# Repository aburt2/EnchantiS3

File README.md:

# EnchantiS3
 Repository for hardware and firmware for the EnchantiS3 board. The EnchantiS3 is a board based on the ESP32-S3 WROOM 2 module from Espressif. It includes a fuel gauge and inertial measurement unit (IMU). The board can be powered from both the USB-C port or a 3.7V lithium ion battery.

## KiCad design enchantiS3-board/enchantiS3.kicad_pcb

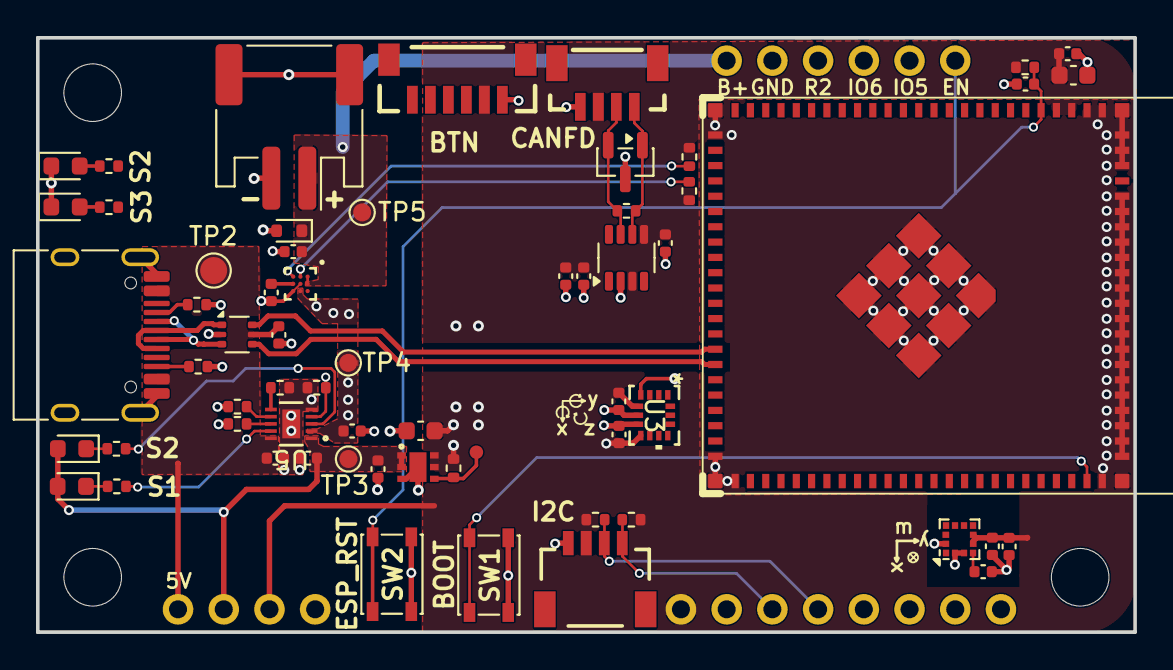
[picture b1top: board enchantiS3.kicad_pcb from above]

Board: 4 copper layers, 61.0 x 33.0 mm, 66 parts (0 on the bottom side), 33 nets.

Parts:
BAT1: JST_SMD_2.0; Battery_JST_2pin
BOARDLAYOUT1: LAYOUT; enchantis31-layout
C1, C5, C6, C9, C11, C16: 1uF; C_0402_1005Metric
C2, C7, C8, C12, C14, C15, C19, C20: 0.1uF; C_0402_1005Metric
C3: 2.2uF; C_0402_1005Metric
C4: 10uF; C_0402_1005Metric
C10, C13: 10uF; C_0603_1608Metric
C17: 0.47uF; C_0402_1005Metric
D1: DZ2S051X0L; D_SOD-523
D2: NUP2105L; SOT-23
H1, H2, H3: MountingHole; MountingHole_3.2mm_M3_DIN965
J1: USB_C_Receptacle_USB2.0; USB_C_Receptacle_HRO_TYPE-C-31-M-12
J2: Conn_01x06; JST_1x06_P1.0mm_Vertical_SMD
J3: Qwiic_Connector; JST_1x04_P1.0mm_Horizontal_SMD
LED1: Orange; LED_0603_1608Metric
LED2: Blue; LED_0603_1608Metric
LED3: Yellow; LED_0603_1608Metric
LED4: Red; LED_0603_1608Metric
R3, R4: 2k; R_0402_1005Metric
R5, R6, R15, R19: 10k; R_0402_1005Metric
R7, R9, R17, R18: 2k2; R_0402_1005Metric
R8, R10: 1k; R_0402_1005Metric
R11, R13: 5K1; R_0402_1005Metric
R12: 13k; R_0402_1005Metric
R14: 0.43k; R_0402_1005Metric
R16: 120; R_0402_1005Metric
SW1: BOOT; SW_SPST_PTS810
SW2: ESP_RST; SW_SPST_PTS810
TOUCH2: JST-SH-1x04 1.0mm; JST_SMD_1.0mm-4_Vertical
TP1: 0.75mm; TestPoint-0.75mm
TP2: TestPoint; TestPoint_Pad_D1.5mm
TP3, TP4, TP5: TestPoint; TestPoint_Pad_D1.0mm
U1: USBLC6-2P6; SOT-666
U2: NCP187; NCV8187_ONS
U3: ICM-42670-P; LGA14_2P5X3X0P91_TDK
U4: ESP32-S31-WROOM-3
U5: BQ25185DLHR; WSON10_DLH_TEX
U6: MAX17262REWL+T; MAX17262
U7: TCAN3413DDFR; TSOT-23-8_DDF_TEX
U8: LIS3MDL; LGA-12_2x2mm_P0.5mm

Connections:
+3V3: BOARDLAYOUT1.2.1 (3v3), BOARDLAYOUT1.3.3 (VDD), C2.1, C3.1, C6.1, C7.1, C8.1, C10.1, C13.1, C14.1, C16.1, C19.1, J2.2, J3.2 (3v3), R5.2, R6.2, R7.2, R9.2, R17.1, R18.1, TOUCH2.2 (3v3), U2.5 (SNS), U2.6 (OUT), U3.5 (VDDIO), U3.8 (VDD), U4.3 (3V3), U4.4 (3V3), U7.3 (VCC), U7.5 (VIO), U8.5 (Vdd), U8.6 (Vdd_IO)
+BATT: BAT1.1 (+), BOARDLAYOUT1.1.1 (VBAT), C15.1, D1.1 (K), TP5.1 (1_1), U6.A1 (TH), U6.A2 (BATT)
/MCU/BOOT: SW1.1, U4.71 (GPIO61)
/MCU/EN: BOARDLAYOUT1.1.6 (EN), C9.1, R5.1, SW2.1, U4.5 (EN)
/MCU/USBD+: U1.6 (I/O1), U4.40 (USB_DP)
/MCU/USBD-: U1.4 (I/O2), U4.41 (USB_DM)
/Motion Sensing/C1: C20.1, U8.4 (C1)
/Peripherals/CAN_H: D2.2 (K), R16.2, TOUCH2.3 (SDA), U7.7 (CANH)
/Peripherals/CAN_L: D2.1 (K), R16.1, TOUCH2.4 (SCL), U7.6 (CANL)
/Peripherals/SCL2: BOARDLAYOUT1.2.3 (SCL), J3.4 (SCL), R7.1
/Peripherals/SDA2: BOARDLAYOUT1.2.4 (SDA), J3.3 (SDA), R9.1
/Power System/FG_SCL: R18.2, U6.B1 (SCL)
/Power System/FG_SDA: R17.2, U6.C1 (SDA)
/Power System/ISET: R14.1, U5.8 (ISET)
/Power System/LED0: LED4.1 (K), R4.1
/Power System/LED1: LED3.1 (K), R3.1
/Power System/PG: R6.1, TP1.1 (1_1), U2.4 (PG)
/Power System/REG: C17.1, U6.C2 (REG)
/Power System/STAT1: R3.2, U5.9 (STAT1)
/Power System/STAT2: R4.2, U5.3 (STAT2)
/Power System/TS: R15.2, U5.6 (TS/MR)
/Power System/VSET: R12.1, U5.7 (ILIM/VSET)
/Power System/~CE: R19.2, U5.4 (~CE)
/USB/CC1: J1.A5 (CC1), R11.1
/USB/CC2: J1.B5 (CC2), R13.1
/USB/D+: J1.A6 (D+), J1.B6 (D+), U1.1 (I/O1)
/USB/D-: J1.A7 (D-), J1.B7 (D-), U1.3 (I/O2)
CHRG+: C5.1, TP4.1 (1_1), U5.2 (BAT), U6.B3 (SYS)
GND: BAT1.2 (-), BAT1.MP (mp), BOARDLAYOUT1.1.2 (GND), BOARDLAYOUT1.2.2 (GND), BOARDLAYOUT1.2.8 (GND), BOARDLAYOUT1.3.4 (GND), C1.2, C2.2, C3.2, C4.2, C5.2, C6.2, C7.2, C8.2, C9.2, C10.2, C11.2, C12.2, C13.2, C14.2, C15.2, C16.2, C17.2, C19.2, C20.2, D1.2 (A), D2.3 (A), J1.A1 (GND), J1.A12 (GND), J1.B1 (GND), J1.B12 (GND), J1.SH (SHIELD), J2.1, J3.1 (GND), LED1.1 (K), LED2.1 (K), R11.2, R12.2, R13.2, R14.2, R15.1, R19.1, SW1.2, SW2.2, TOUCH2.1 (GND), U1.2 (GND), U2.3 (GND), U2.7 (GND), U3.6 (GND), U3.7 (FSYNC), U4.1 (GND), U4.2 (GND), U4.26 (GND), U4.47 (GND), U4.48 (GND), U4.72 (GND), U4.73 (GND), U4.74 (GND), U4.75 (GND), U4.76 (GND), U4.77 (GND), U4.78 (GND), U4.79 (GND), U4.80 (GND), U4.81 (GND), U4.82 (GND), U4.83 (GND), U4.84 (GND), U4.85 (GND), U4.86 (GND), U4.87 (GND), U4.88 (GND), U4.89 (GND), U4.90 (GND), U4.92 (GND), U4.93 (GND), U4.94 (GND), U4.95 (GND), U4.96 (GND), U4.97 (GND), U4.98 (GND), U4.99 (GND), U5.5 (GND), U5.11 (EPAD), U6.B2 (ALRT), U6.C3 (GND), U7.2 (GND), U8.2 (GND), U8.3 (GND), U8.12 (GND)
unnamed: LED1.2 (A), R10.2
unnamed: LED2.2 (A), R8.2
SYS: BOARDLAYOUT1.3.2 (SYS), C4.1, C11.1, LED3.2 (A), LED4.2 (A), TP3.1 (1_1), U2.1 (IN), U2.2 (EN), U5.1 (SYS)
VUSB: BOARDLAYOUT1.3.1 (5v), C1.1, C12.1, J1.A4 (VBUS), J1.A9 (VBUS), J1.B4 (VBUS), J1.B9 (VBUS), TP2.1 (1_1), U1.5 (VBUS), U5.10 (IN)

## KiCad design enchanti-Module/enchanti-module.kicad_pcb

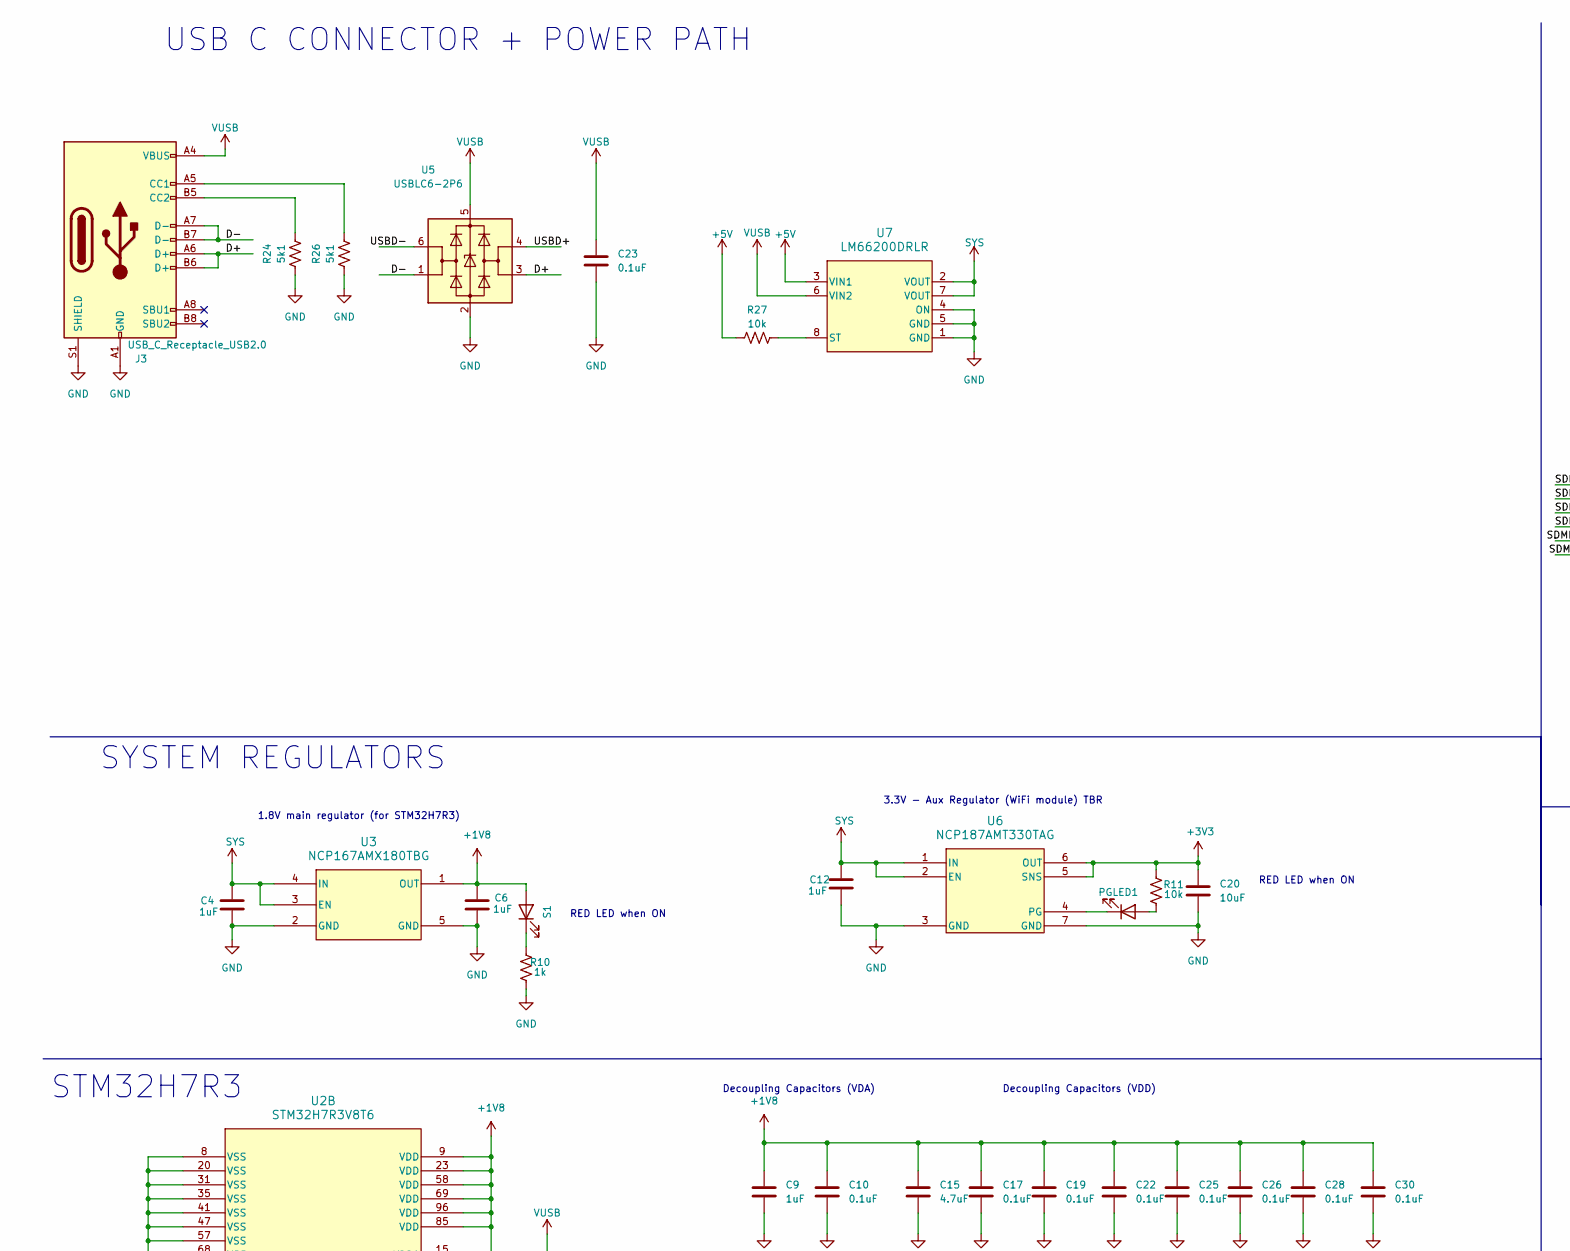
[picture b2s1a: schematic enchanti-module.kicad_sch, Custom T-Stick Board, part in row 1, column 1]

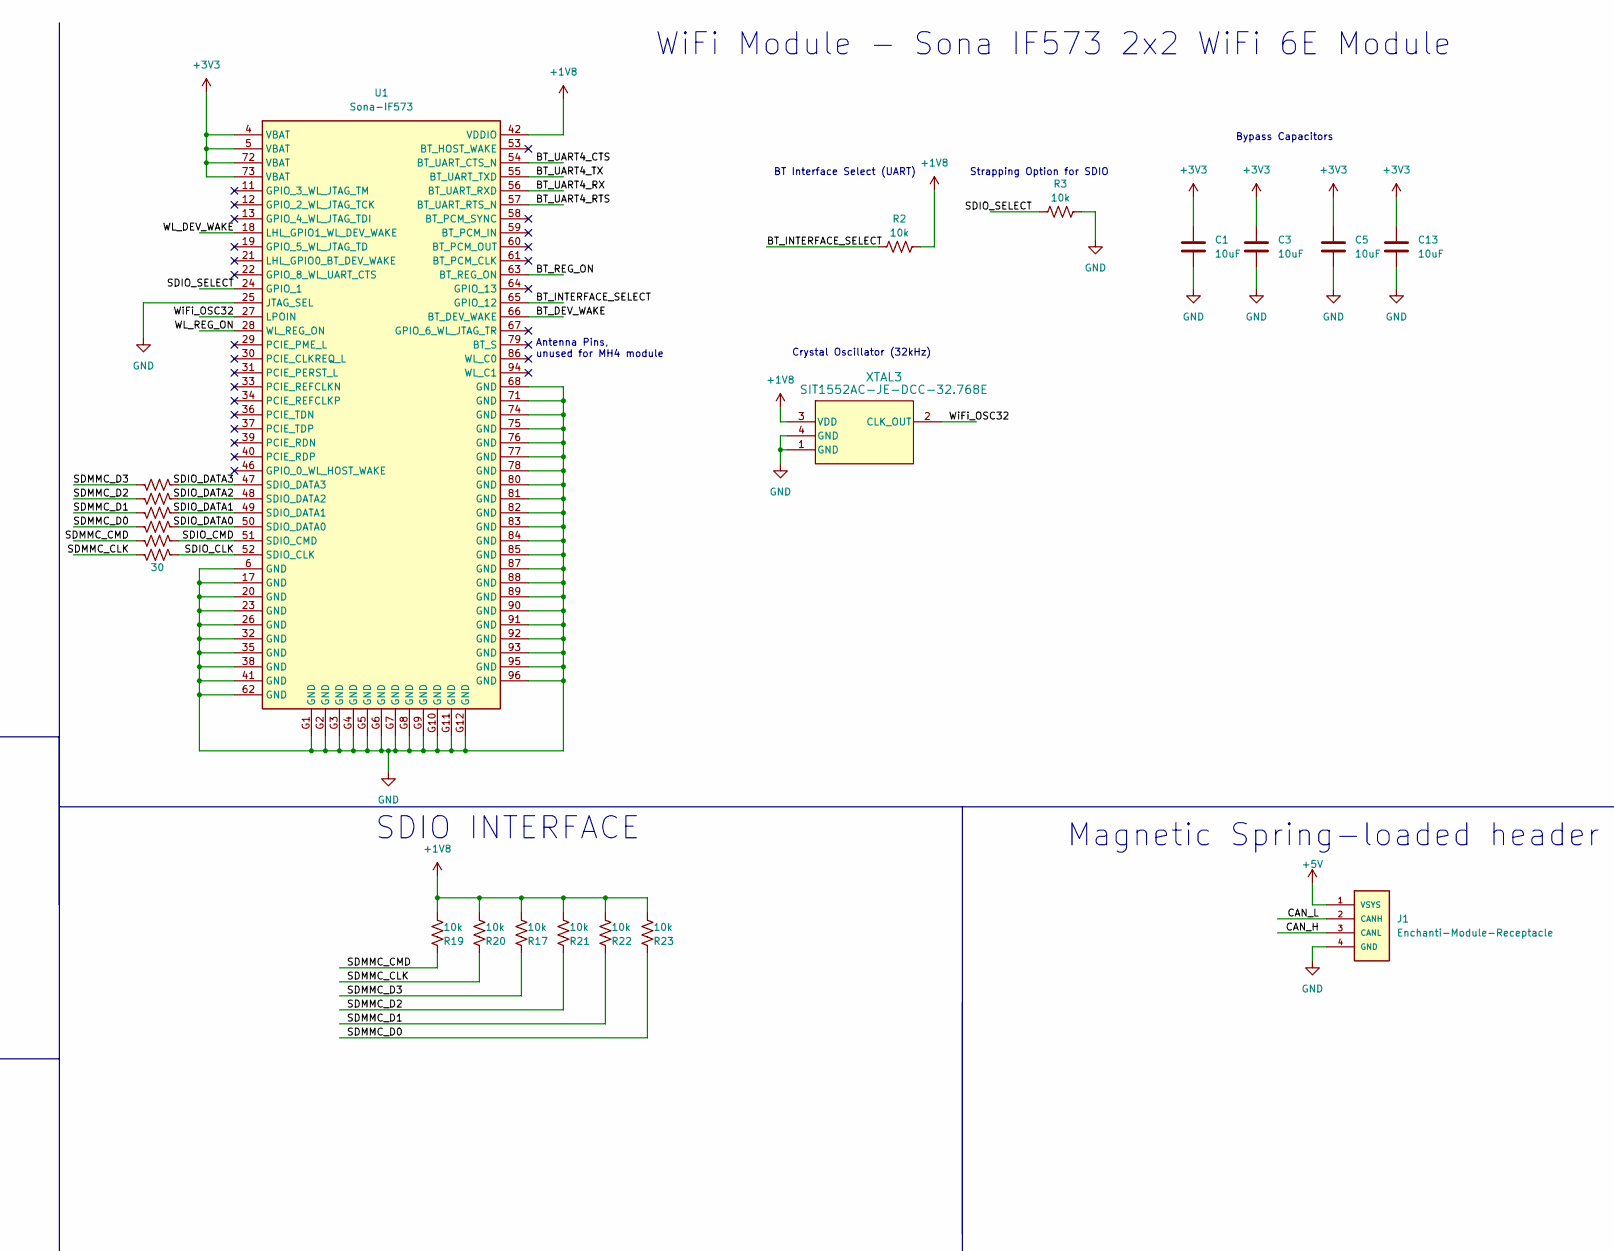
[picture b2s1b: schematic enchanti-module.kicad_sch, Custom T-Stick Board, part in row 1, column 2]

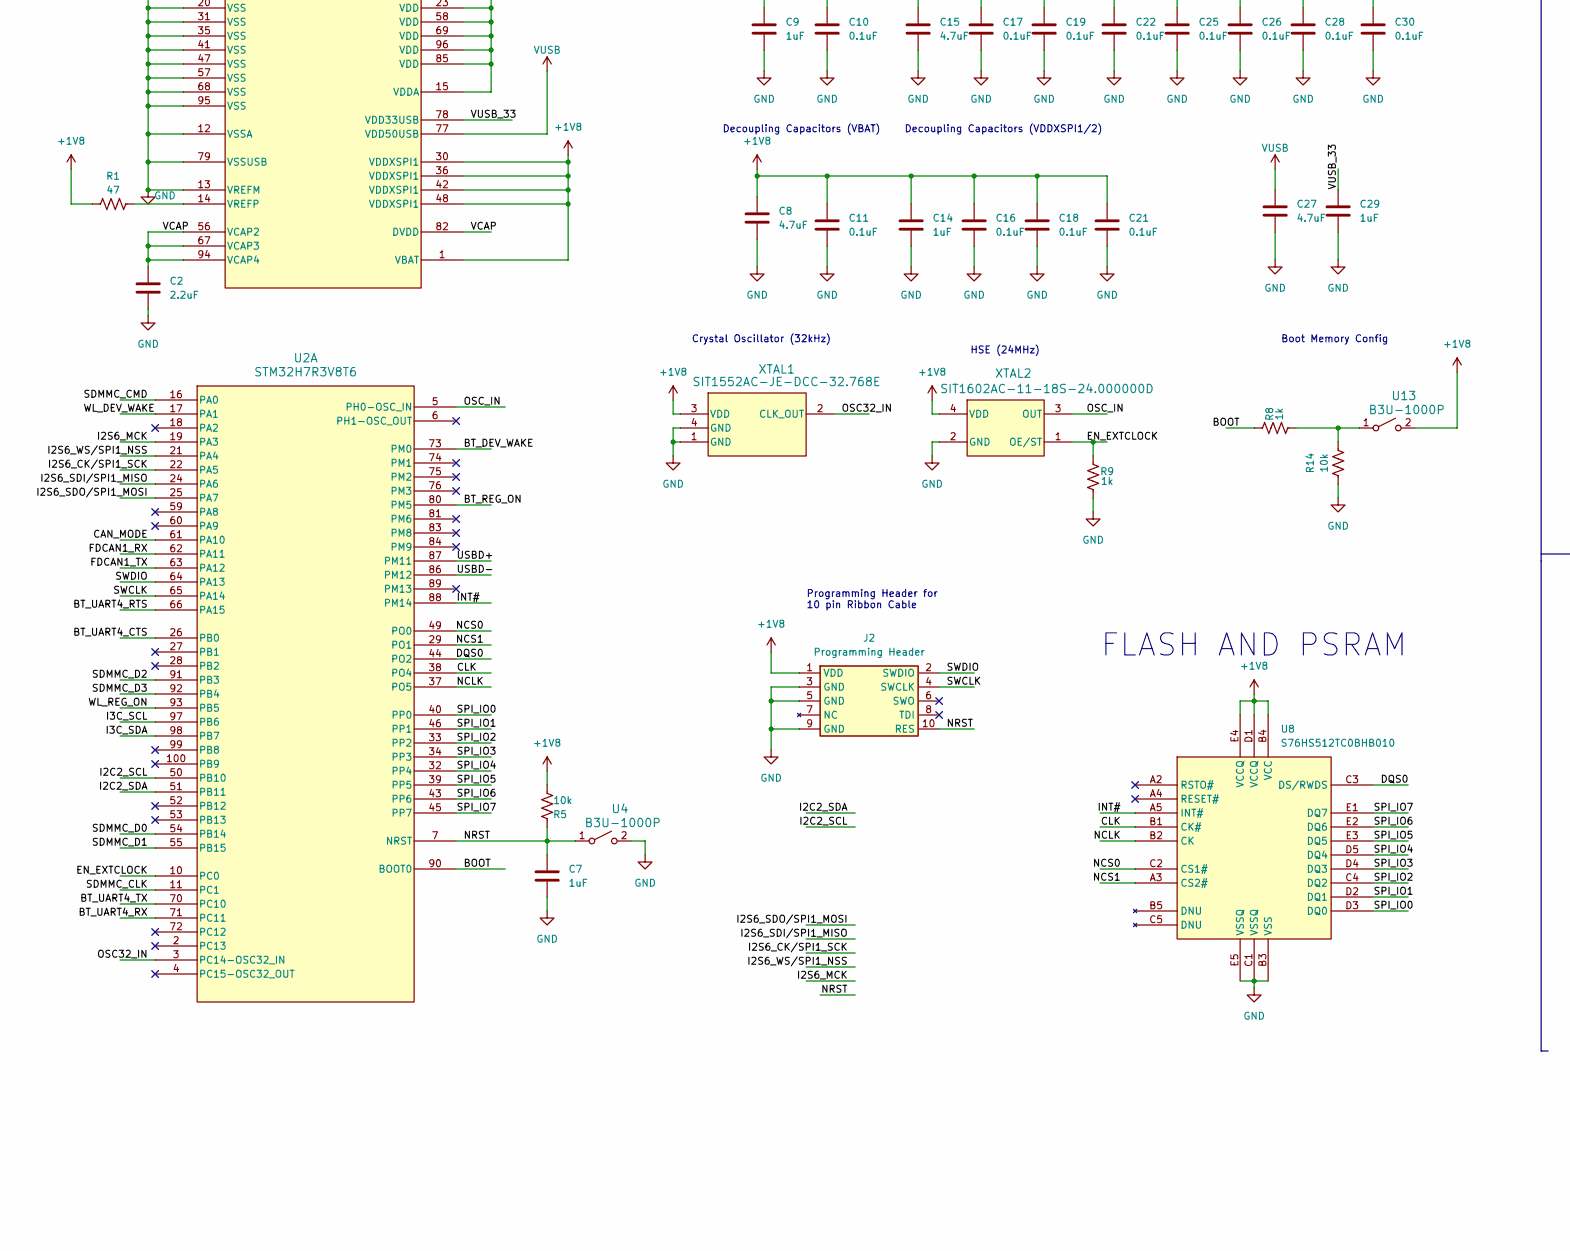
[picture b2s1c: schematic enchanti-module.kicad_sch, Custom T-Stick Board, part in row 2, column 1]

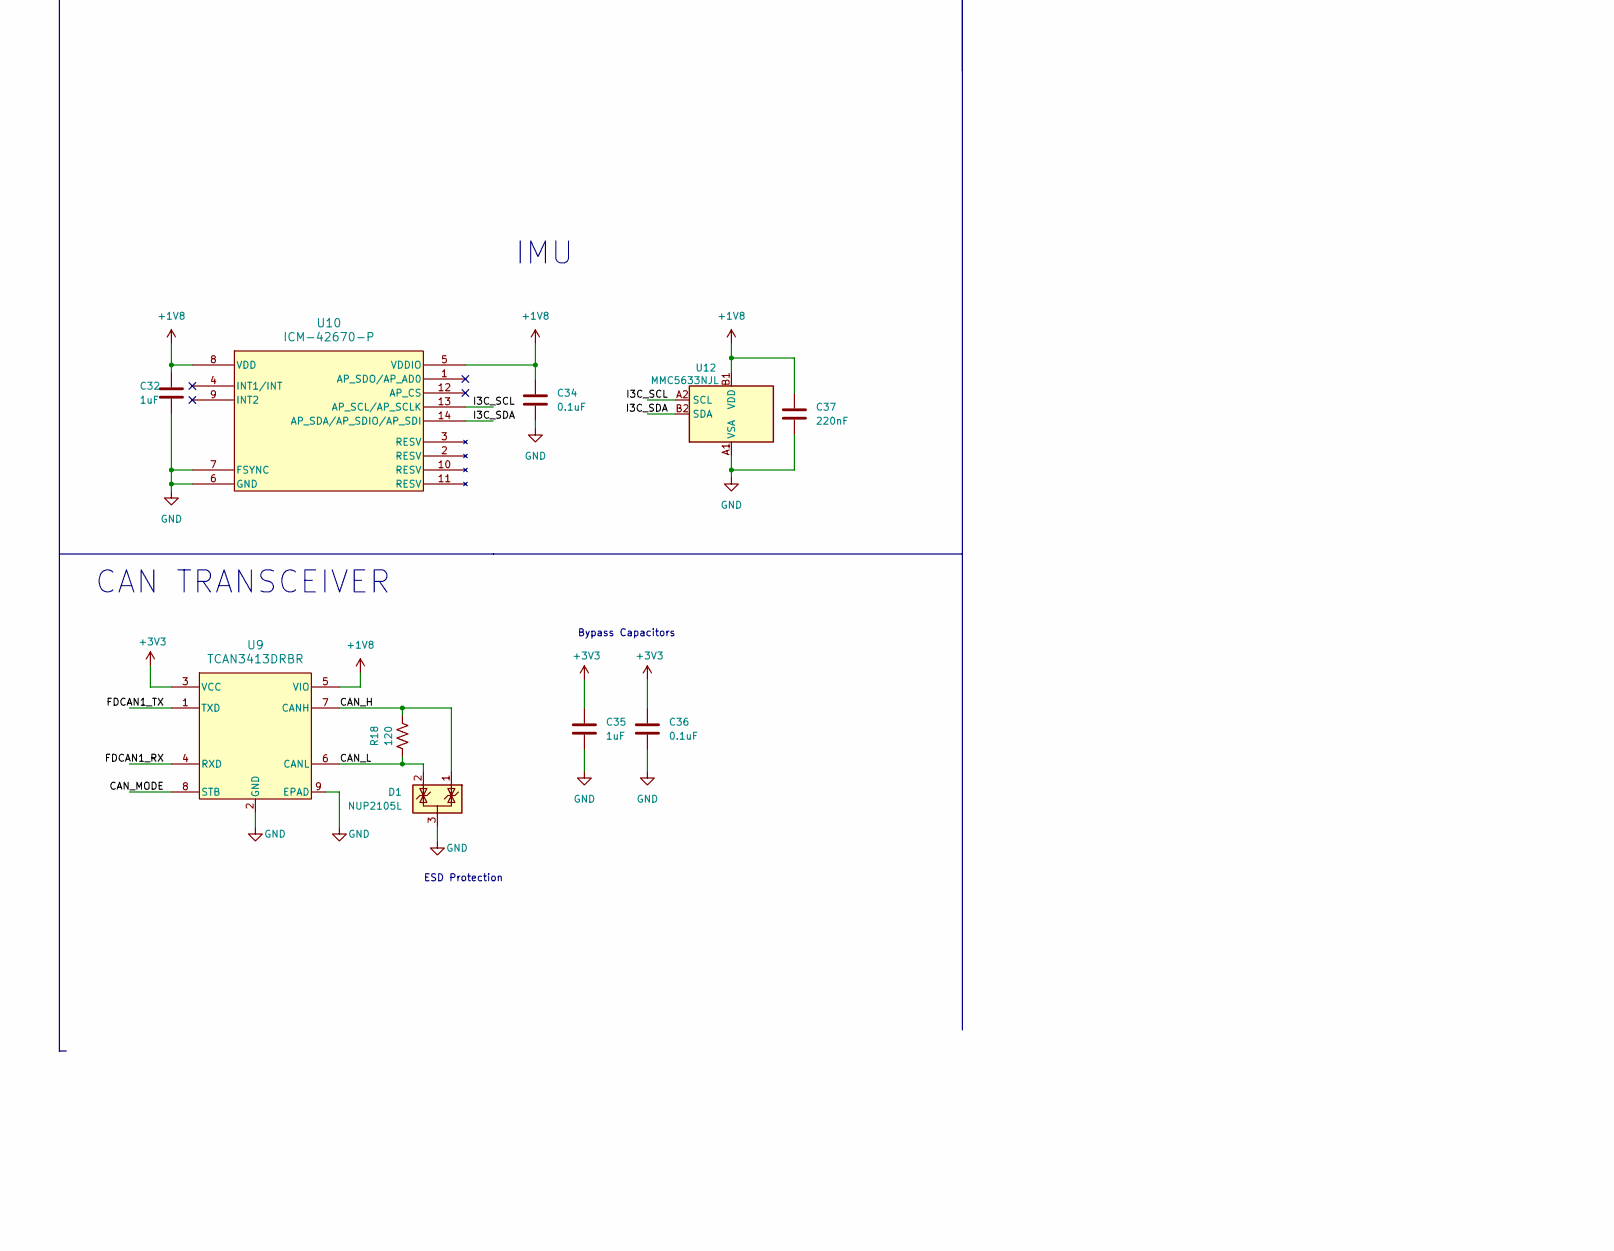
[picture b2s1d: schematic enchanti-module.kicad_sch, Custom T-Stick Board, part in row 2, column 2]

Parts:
C1, C3, C5, C13, C20: 10uF; C_0603_1608Metric; Mfg Part # CL10A106KO8NNNC
C2: 2.2uF; C_0603_1608Metric; Mfg Part # CL10A225KO8NNNC
C4, C6, C7, C9, C12, C14, C29, C32, C35: 1uF; C_0402_1005Metric; Mfg Part # CL05A105KO5NNNC
C8, C15, C27: 4.7uF; C_0603_1608Metric; Mfg Part # CL10A475KO8NNNC
C10, C11, C16, C17, C18, C19, C21, C22, C23, C25, C26, C28, C30, C34, C36: 0.1uF; C_0402_1005Metric; Mfg Part # CL05B104KO5NNNC
C37: 220nF; C_0402_1005Metric; Mfg Part # CL05B224KO5NNNC
D1: NUP2105L; SOT-23; Mfg Part # NUP2105L
J1: Enchanti-Module-Receptacle; Mfg Part # S70-332002045R (x4)
J2: Programming Header; SAMTEC_FTSH-105-01-F-DV-P-TR; Mfg Part # FTSH-105-01-F-DV-K-TR
J3: USB_C_Receptacle_USB2.0; USB_C_Receptacle_GCT_USB4105-xx-A_16P_TopMnt_Horizontal; Mfg Part # USB4105-GF-A
PGLED1: PGLED1; LED_0402_1005Metric; Mfg Part # APHHS1005SURCK
PGLED2: S1; LED_0402_1005Metric; Mfg Part # APHHS1005SURCK
R1: 47; R_0402_1005Metric; Mfg Part # ERJ-2RKF47R0X
R2, R3, R5, R11, R14, R17, R19, R20, R21, R22, R23, R27: 10k; R_0402_1005Metric; Mfg Part # ERJ-2RKF1002X
R4, R6, R7, R12, R13, R25: 30; R_0402_1005Metric; Mfg Part # ERJ-2RKF30R0X
R8, R9, R10: 1k; R_0402_1005Metric; Mfg Part # ERJ-2RKF1001X
R18: 120; R_0402_1005Metric; Mfg Part # ERJ-2RKF2201X
R24, R26: 5k1; R_0402_1005Metric; Mfg Part # ERJ-2RKF5101X
SYS1, SYS2, SYS4: SYS
U1: Sona-IF573; Mfg Part # 453-00117C
U2: STM32H7R3V8T6; LQFP-100_STM; Mfg Part # STM32H7R3V8T6
U3: NCP167AMX180TBG; XDFN4_1X1_711AJ_ONS; Mfg Part # NCP167AMX180TBG
U4, U13: B3U-1000P; Mfg Part # B3U-1000P
U5: USBLC6-2P6; SOT-666; Mfg Part # USBLC6-2P6
U6: NCP187AMT330TAG; NCV8187AMT330TAG_ONS-L; Mfg Part # NCP187AMT330TAG
U7: LM66200DRLR; SOT-5X3_DRL_TEX; Mfg Part # LM66200DRLR
U8: S76HS512TC0BHB010; BGA24C100P5X5_800X800X120; Mfg Part # S76HS512TC0BHB010
U9: TCAN3413DRBR; VSON8-DRB_TEX; Mfg Part # TCAN3413DRBR
U10: ICM-42670-P; LGA14_2P5X3X0P91_TDK; Mfg Part # ICM-42670-P
U12: MMC5633NJL; WLP-4_0.86x0.86mm_P0.4mm; Mfg Part # MMC5633NJL
XTAL1, XTAL3: SIT1552AC-JE-DCC-32.768E; BGA4_SiT1532_SIT; Mfg Part # SIT1552AC-JE-DCC-32.768E
XTAL2: SIT1602AC-11-18S-24.000000D; SON4_CS00119_SIT; Mfg Part # SIT1602AC-11-18S-24.000000D

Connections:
+1V8: C6.1, C8.1, C9.1, C10.1, C11.1, C14.1, C15.1, C16.1, C17.1, C18.1, C19.1, C21.1, C22.1, C25.1, C26.1, C28.1, C30.1, C32.1, C34.1, C37.1, J2.1 (VDD), PGLED2.2 (A), R1.1, R2.2, R5.1, R17.1, R19.1, R20.1, R21.1, R22.1, R23.1, U1.42 (VDDIO), U2.1 (VBAT), U2.9 (VDD), U2.15 (VDDA), U2.23 (VDD), U2.30 (VDDXSPI1), U2.36 (VDDXSPI1), U2.42 (VDDXSPI1), U2.48 (VDDXSPI1), U2.58 (VDD), U2.69 (VDD), U2.85 (VDD), U2.96 (VDD), U3.1 (OUT), U8.B4 (VCC), U8.D1 (VCCQ), U8.E4 (VCCQ), U9.5 (VIO), U10.5 (VDDIO), U10.8 (VDD), U12.B1 (VDD), U13.2, XTAL1.3 (VDD), XTAL2.4 (VDD), XTAL3.3 (VDD)
+3V3: C1.1, C3.1, C5.1, C13.1, C20.1, C35.1, C36.1, R11.1, U1.4 (VBAT), U1.5 (VBAT), U1.72 (VBAT), U1.73 (VBAT), U6.5 (SNS), U6.6 (OUT), U9.3 (VCC)
+5V: J1.1 (VSYS), R27.1, U7.3 (VIN1)
/BOOT: R8.1, U2.90 (BOOT0)
/BT_DEV_WAKE: U1.66 (BT_DEV_WAKE), U2.73 (PM0)
/BT_INTERFACE_SELECT: R2.1, U1.65 (GPIO_12)
/BT_REG_ON: U1.63 (BT_REG_ON), U2.80 (PM5)
/BT_UART4_CTS: U1.54 (BT_UART_CTS_N), U2.26 (PB0)
/BT_UART4_RTS: U1.57 (BT_UART_RTS_N), U2.66 (PA15)
/BT_UART4_RX: U1.56 (BT_UART_RXD), U2.71 (PC11)
/BT_UART4_TX: U1.55 (BT_UART_TXD), U2.70 (PC10)
/CAN_H: D1.1 (K), J1.3 (CANL), R18.2, U9.7 (CANH)
/CAN_L: D1.2 (K), J1.2 (CANH), R18.1, U9.6 (CANL)
/CAN_MODE: U2.61 (PA10), U9.8 (STB)
/CLK: U2.38 (PO4), U8.B1 (CK#)
/D+: J3.A6 (D+), J3.B6 (D+), U5.3 (I/O2)
/D-: J3.A7 (D-), J3.B7 (D-), U5.1 (I/O1)
/DQS0: U2.44 (PO2), U8.C3 (DS/RWDS)
/EN_EXTCLOCK: R9.1, U2.10 (PC0), XTAL2.1 (OE/ST)
/FDCAN1_RX: U2.62 (PA11), U9.4 (RXD)
/FDCAN1_TX: U2.63 (PA12), U9.1 (TXD)
/I2C2_SCL: U2.50 (PB10)
/I2C2_SDA: U2.51 (PB11)
/I2S6_CK/SPI1_SCK: U2.22 (PA5)
/I2S6_MCK: U2.19 (PA3)
/I2S6_SDI/SPI1_MISO: U2.24 (PA6)
/I2S6_SDO/SPI1_MOSI: U2.25 (PA7)
/I2S6_WS/SPI1_NSS: U2.21 (PA4)
/I3C_SCL: U2.97 (PB6), U10.13 (AP_SCL/AP_SCLK), U12.A2 (SCL)
/I3C_SDA: U2.98 (PB7), U10.14 (AP_SDA/AP_SDIO/AP_SDI), U12.B2 (SDA)
/INT#: U2.88 (PM14), U8.A5 (INT#)
/NCLK: U2.37 (PO5), U8.B2 (CK)
/NCS0: U2.49 (PO0), U8.C2 (CS1#)
/NCS1: U2.29 (PO1), U8.A3 (CS2#)
/NRST: C7.1, J2.10 (RES), R5.2, U2.7 (NRST), U4.1
/OSC32_IN: U2.3 (PC14-OSC32_IN), XTAL1.2 (CLK_OUT)
/OSC_IN: U2.5 (PH0-OSC_IN), XTAL2.3 (OUT)
/SDIO_CLK: R6.1, U1.52 (SDIO_CLK)
/SDIO_CMD: R4.1, U1.51 (SDIO_CMD)
/SDIO_DATA0: R25.1, U1.50 (SDIO_DATA0)
/SDIO_DATA1: R13.1, U1.49 (SDIO_DATA1)
/SDIO_DATA2: R12.1, U1.48 (SDIO_DATA2)
/SDIO_DATA3: R7.1, U1.47 (SDIO_DATA3)
/SDIO_SELECT: R3.1, U1.24 (GPIO_1)
/SDMMC_CLK: R6.2, R20.2, U2.11 (PC1)
/SDMMC_CMD: R4.2, R19.2, U2.16 (PA0)
/SDMMC_D0: R23.2, R25.2, U2.54 (PB14)
/SDMMC_D1: R13.2, R22.2, U2.55 (PB15)
/SDMMC_D2: R12.2, R21.2, U2.91 (PB3)
/SDMMC_D3: R7.2, R17.2, U2.92 (PB4)
/SPI_IO0: U2.40 (PP0), U8.D3 (DQ0)
/SPI_IO1: U2.46 (PP1), U8.D2 (DQ1)
/SPI_IO2: U2.33 (PP2), U8.C4 (DQ2)
/SPI_IO3: U2.34 (PP3), U8.D4 (DQ3)
/SPI_IO4: U2.32 (PP4), U8.D5 (DQ4)
/SPI_IO5: U2.39 (PP5), U8.E3 (DQ5)
/SPI_IO6: U2.43 (PP6), U8.E2 (DQ6)
/SPI_IO7: U2.45 (PP7), U8.E1 (DQ7)
/SWCLK: J2.4 (SWCLK), U2.65 (PA14)
/SWDIO: J2.2 (SWDIO), U2.64 (PA13)
/USBD+: U2.87 (PM11), U5.4 (I/O2)
/USBD-: U2.86 (PM12), U5.6 (I/O1)
/VCAP: C2.1, U2.56 (VCAP2), U2.67 (VCAP3), U2.82 (DVDD), U2.94 (VCAP4)
/VUSB_33: C29.1, U2.78 (VDD33USB)
/WL_DEV_WAKE: U1.18 (LHL_GPIO1_WL_DEV_WAKE), U2.17 (PA1)
/WL_REG_ON: U1.28 (WL_REG_ON), U2.93 (PB5)
/WiFi_OSC32: U1.27 (LPOIN), XTAL3.2 (CLK_OUT)
GND: C1.2, C2.2, C3.2, C4.2, C5.2, C6.2, C7.2, C8.2, C9.2, C10.2, C11.2, C12.2, C13.2, C14.2, C15.2, C16.2, C17.2, C18.2, C19.2, C20.2, C21.2, C22.2, C23.2, C25.2, C26.2, C27.2, C28.2, C29.2, C30.2, C32.2, C34.2, C35.2, C36.2, C37.2, D1.3 (A), J1.4 (GND), J2.3 (GND), J2.5 (GND), J2.9 (GND), J3.A1 (GND), J3.A12 (GND), J3.B1 (GND), J3.B12 (GND), J3.S1 (SHIELD), R3.2, R9.2, R10.2, R14.1, R24.1, R26.1, U1.6 (GND), U1.17 (GND), U1.20 (GND), U1.23 (GND), U1.25 (JTAG_SEL), U1.26 (GND), U1.32 (GND), U1.35 (GND), U1.38 (GND), U1.41 (GND), U1.62 (GND), U1.68 (GND), U1.71 (GND), U1.74 (GND), U1.75 (GND), U1.76 (GND), U1.77 (GND), U1.78 (GND), U1.80 (GND), U1.81 (GND), U1.82 (GND), U1.83 (GND), U1.84 (GND), U1.85 (GND), U1.87 (GND), U1.88 (GND), U1.89 (GND), U1.90 (GND), U1.91 (GND), U1.92 (GND), U1.93 (GND), U1.95 (GND), U1.96 (GND), U1.G1 (GND), U1.G2 (GND), U1.G3 (GND), U1.G4 (GND), U1.G5 (GND), U1.G6 (GND), U1.G7 (GND), U1.G8 (GND), U1.G9 (GND), U1.G10 (GND), U1.G11 (GND), U1.G12 (GND), U2.8 (VSS), U2.12 (VSSA), U2.13 (VREFM), U2.20 (VSS), U2.31 (VSS), U2.35 (VSS), U2.41 (VSS), U2.47 (VSS), U2.57 (VSS), U2.68 (VSS), U2.79 (VSSUSB), U2.95 (VSS), U3.2 (GND), U3.5 (GND), U4.2, U5.2 (GND), U6.3 (GND), U6.7 (GND), U7.1 (GND), U7.4 (ON), U7.5 (GND), U8.B3 (VSS), U8.C1 (VSSQ), U8.E5 (VSSQ), U9.2 (GND), U9.9 (EPAD), U10.6 (GND), U10.7 (FSYNC), U12.A1 (VSA), XTAL1.1 (GND), XTAL1.4 (GND), XTAL2.2 (GND), XTAL3.1 (GND), XTAL3.4 (GND)
unnamed: J3.A5 (CC1), R26.2
unnamed: J3.B5 (CC2), R24.2
unnamed: PGLED1.2 (A), R11.2
unnamed: PGLED1.1 (K), U6.4 (PG)
unnamed: PGLED2.1 (K), R10.1
unnamed: R8.2, R14.2, U13.1
unnamed: R1.2, U2.14 (VREFP)
unnamed: R27.2, U7.8 (ST)
VUSB: C23.1, C27.1, J3.A4 (VBUS), J3.A9 (VBUS), J3.B4 (VBUS), J3.B9 (VBUS), U2.77 (VDD50USB), U5.5 (VBUS), U7.6 (VIN2)

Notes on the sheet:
Decoupling Capacitors (VDDXSPI1/2)
SDIO INTERFACE
Decoupling Capacitors (VBAT)
Bypass Capacitors
1.8V main regulator (for STM32H7R3)
RED LED when ON
BT Interface Select (UART)
IMU
Crystal Oscillator (32kHz)
Programming Header for 10 pin Ribbon Cable
STM32H7R3
Decoupling Capacitors (VDD)
Magnetic Spring-loaded header
FLASH AND PSRAM
Antenna Pins, unused for MH4 module
SYSTEM REGULATORS
WiFi Module - Sona IF573 2x2 WiFi 6E Module
3.3V - Aux Regulator (WiFi module) TBR
HSE (24MHz)
ESD Protection
USB C CONNECTOR + POWER PATH
Decoupling Capacitors (VDA)
Boot Memory Config
Strapping Option for SDIO
CAN TRANSCEIVER

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
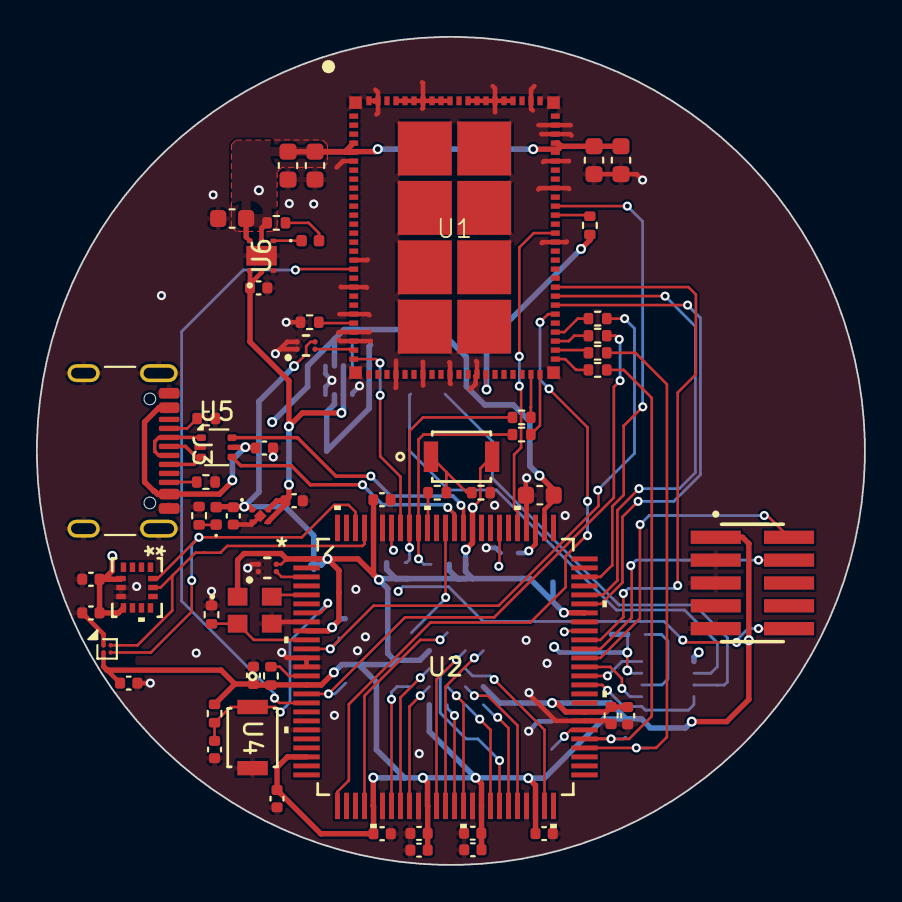
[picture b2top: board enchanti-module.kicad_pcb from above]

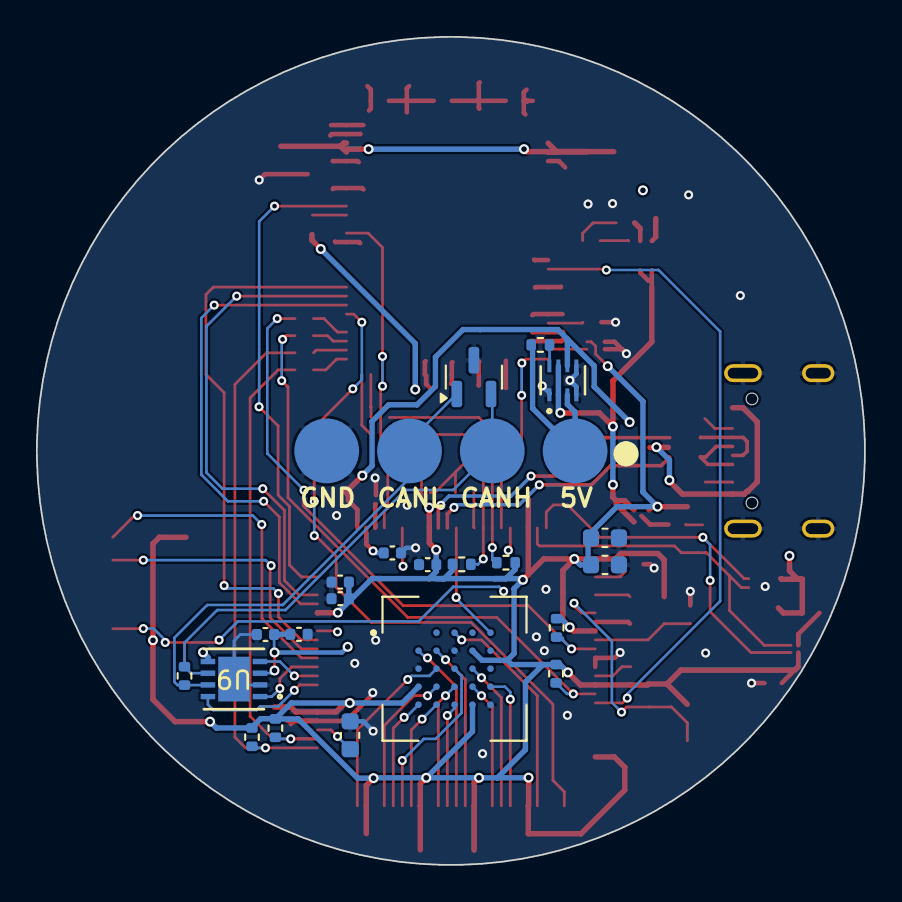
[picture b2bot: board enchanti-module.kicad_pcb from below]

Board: 4 copper layers, 46.0 x 46.0 mm, 80 parts (22 on the bottom side), 71 nets.
